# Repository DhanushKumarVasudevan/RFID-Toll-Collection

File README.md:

View this project on [CADLAB.io](https://cadlab.io/project/29126). 

# RFID-Toll-Collection

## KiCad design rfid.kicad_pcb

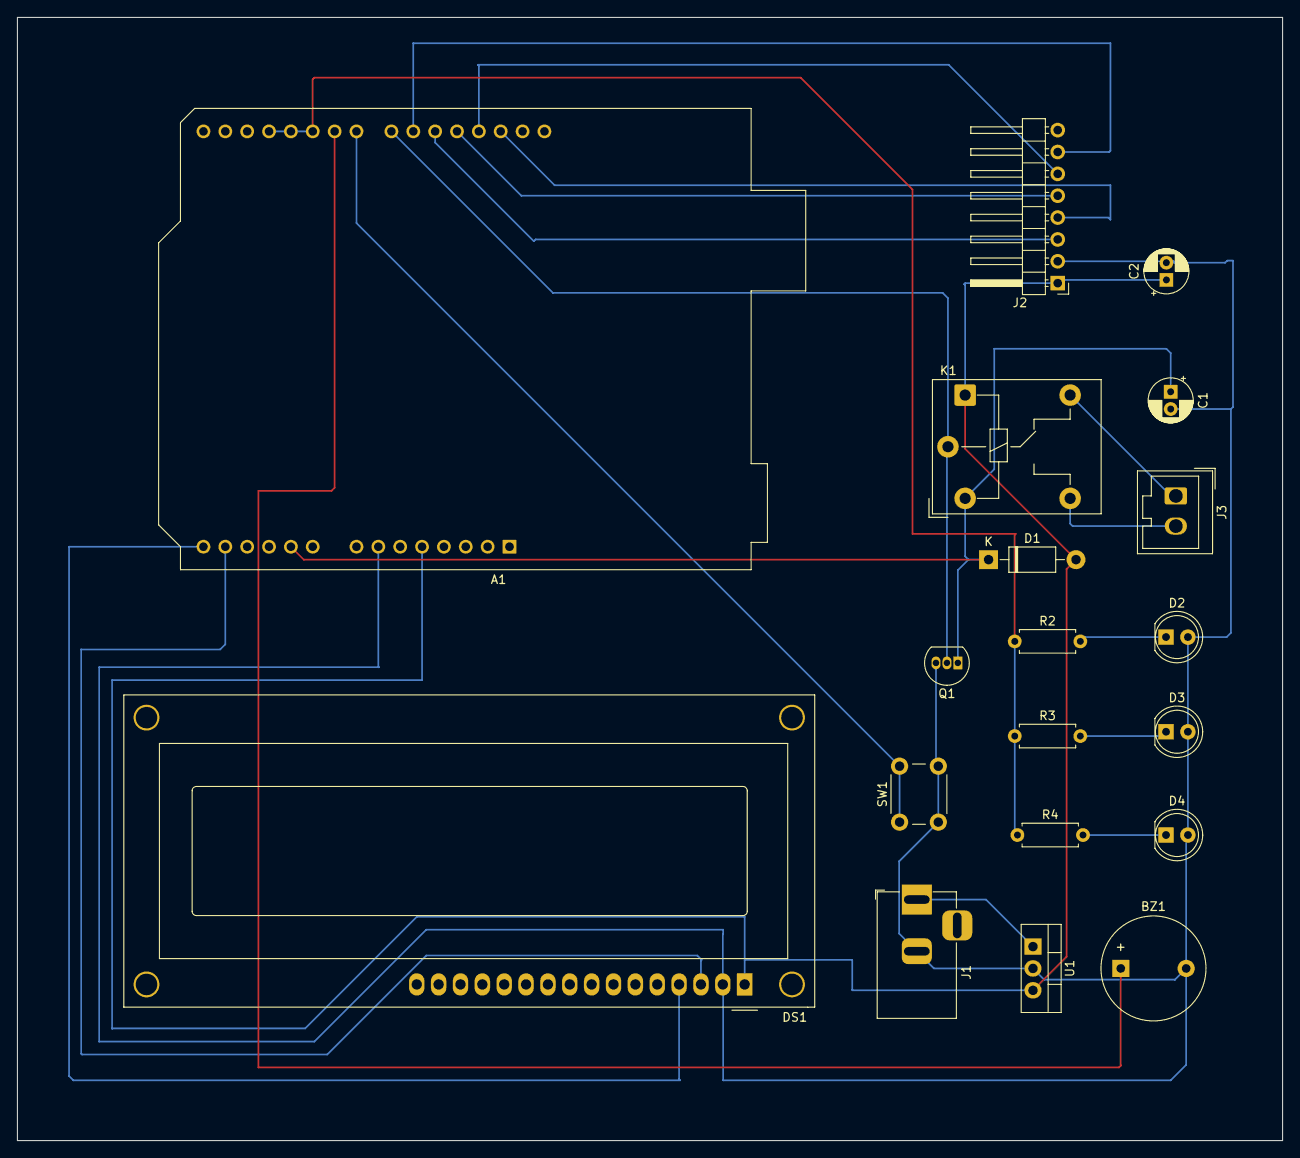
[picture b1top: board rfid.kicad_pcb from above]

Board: 2 copper layers, 147.0 x 130.5 mm, 19 parts (0 on the bottom side), 20 nets.

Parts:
A1: Arduino_UNO_R2
BZ1: Buzzer; Buzzer_12x9.5RM7.6
C1, C2: C; CP_Radial_D5.0mm_P2.00mm
D1: 1N4007; D_DO-41_SOD81_P10.16mm_Horizontal
D2, D3, D4: LED; LED_D5.0mm
DS1: WC1602A
J1: Barrel_Jack; BarrelJack_Horizontal
J2: Conn_01x08_Pin; PinHeader_1x08_P2.54mm_Horizontal
J3: Screw_Terminal_01x02; Wago_734-132_1x02_P3.50mm_Vertical
K1: Relay_SPDT; Relay_SPDT_Hongfa_HF3F-L-xx-1ZL1T
Q1: BC547; TO-92_Inline
R2, R3, R4: R; R_Axial_DIN0207_L6.3mm_D2.5mm_P7.62mm_Horizontal
SW1: SW_Push; SW_PUSH_6mm
U1: L7805; TO-220-3_Vertical

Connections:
+5V: A1.5 (+5V), C2.1, D1.2 (A), DS1.1 (VSS), J2.1, K1.A1, U1.3 (OUT)
+12V: J1.1, U1.1 (IN)
/220 ohm: A1.18 (D3), A1.19 (D4), A1.20 (D5), R2.1, R3.1, R4.1
/BTN out: A1.22 (D7), SW1.1
/Buzzer_out: A1.21 (D6), BZ1.1 (+)
/LCD_SCL: A1.14 (SCL/A5), DS1.4 (RS)
/LCD_SDA: A1.13 (SDA/A4), DS1.3 (VO)
/LED1_OUT: D2.1 (K), R2.2
/LED2_OUT: D3.1 (K), R3.2
/LED3_OUT: D4.1 (K), R4.2
/RFID_MISO: A1.27 (D12), J2.6
/RFID_MOSI: A1.26 (D11), J2.5
/RFID_RST: A1.24 (D9), J2.7
/RFID_SCK: A1.28 (D13), J2.4
/RFID_SDA: A1.25 (D10), J2.3
/Relay Common: A1.23 (D8), K1.11, Q1.2 (B)
/Relay Ctrl: A1.10 (A1), C1.1, D1.1 (K), K1.A2, Q1.1 (C)
/Relay OFF: J3.2, K1.14
/Relay ON: J3.1, K1.12
GND: A1.7 (GND), BZ1.2 (-), C1.2, C2.2, D2.2 (A), D3.2 (A), D4.2 (A), DS1.2 (VDD), J1.2, J2.2, Q1.3 (E), SW1.2, U1.2 (GND)

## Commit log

2025-04-01 done
2025-04-01 Backlink to CADLAB.io has been added.
